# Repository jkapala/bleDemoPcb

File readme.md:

# Overview

This project started with the goal of building a circuit around the STM32 architecture and incorporate various features to evaluate them, which are called out in the Specifications document. A major goal of the project was also to document the project here, making sure to share my progress and use version control. Namely, I wanted to build a board to utilize BLE/WiFi directly, using a PIFA PCB or ceramic chip antenna, instead of using a Wireless module PCB as I have done in the past. As that is the primary goal of the project, other features were secondary but I was able to incorporate a lot of the initial specifications I made and even add some that could lend themselves to a compelling demo of the board. Unfortunately, the STM line of chips does not support WiFi so it was decided that it should be exluded from the project and BLE will be the primary wireless protocol used.

The firmware can be located at this repository: https://github.com/jkapala/bleDemoFirmware

**System Diagram**

## 4/7/2025 Update

The Design Output document is done! I have now edited it and reviewed it so that it is now a complete draft that matches the layout and schematic. The schematic has also been reviewed and edited to fix little things and improve readibility. As well, a few changes were made to the schematic and layout. Namely, a header to access the USB VBUS rail after the current sense resitor has been added, a ground pin has been added to the analog input channel header, and the ESD diodes for the SD card were swapped for ones with lower breakdown/clamping voltage.

At this stage, I consider all the design files to be in good standing and in agreement with each other. The next step will be to generate a BOM and scrutinize the pinouts of the selected components to the schematics/layout files.

In summary, I believe this commit is a complete draft of both the schematic, layout, and design output.

**Top View**

**Bottom View**

**Layer View**

## 3/31/2025 Update

Layout of the PCB is finished! I do not expect to change very much now regarding the circuit design or changing the board in any major way. DRC check has run and there are no major issues remaining. Any additional changes should be mainly cosmetic in the PCB and organizational in the schematic files. An additional final check that could necessitate a change is to use the STM32Cube IDE to verify that the pinout for the peripherals is correct, though it was used throughout for this already. The final footprint should focus most interaction to the top of the board. For ease of mounting the referenced LCD character display to the board, a female 2.54mm socket can be attached to the back of the board and the mounting holes in the corners should be aligned so that the screen can be mounted using standoffs/screws.

**Top View**

**Bottom View**

**Layer View**

The schematic should also specify all part numbers in order to generate a BOM in a future commit. Some passives and minor components remain unspecified because of their generic or non-critical parameters, e.g. specific 0603 LEDs.

The next step is to finalize the Hardware Design Output file by editing the current document to remove extra information, unused part numbers, check individual circuit blocks, part schematics, etc etc.

## 3/18/2025 Update

Layout is coming along and I am making my way to the STM32 and audio blocks. I decided to get with a ceramic chip antenna instead of the PCB antenna to increase chance of successful RF performance since I don't have RF tools right now. As such, I am using the spatial feedback of the mapped blocks to make final changes in the schematic. For example, I am most likely going to omit the onboard speaker because it really isn't necessary and I can get the version with the plug instead and use that. It looks like I will want to plan to mount the display on the bottomside of the board, otherwise I will cover any exposed pins. This requires moving the connector. Once I get that and the audio block sorted, the rest of the placement should be fairly straightforward.

## 3/7/2025 Update

Layout has started! Finally. I have made a big push to wrap up the schematic layout and do any corresponding research into the various things I wanted to study while building the board, such as RF theory, audio theory, best high-speed layout practices, EMI/EMC topics, etc etc.
The schematic is largely done and should only need adjustment to address bugs or layout improvements. The layout itself is roughly mapped out and currently is sketched to support mounting the chosen LCD screen directly on top of the board, but this require sizeable footprint so I might scrap that idea as I get more blocks placed. I am currently in the stage of doing the rough placing of components relative to the center component (e.g. the STM32, USB PD chip, DC-DC regulators, audio DAC + amp, etc etc). The USB PD block is done and now I am moving on to the DC-DC converters to route power to the downstream circuitry.

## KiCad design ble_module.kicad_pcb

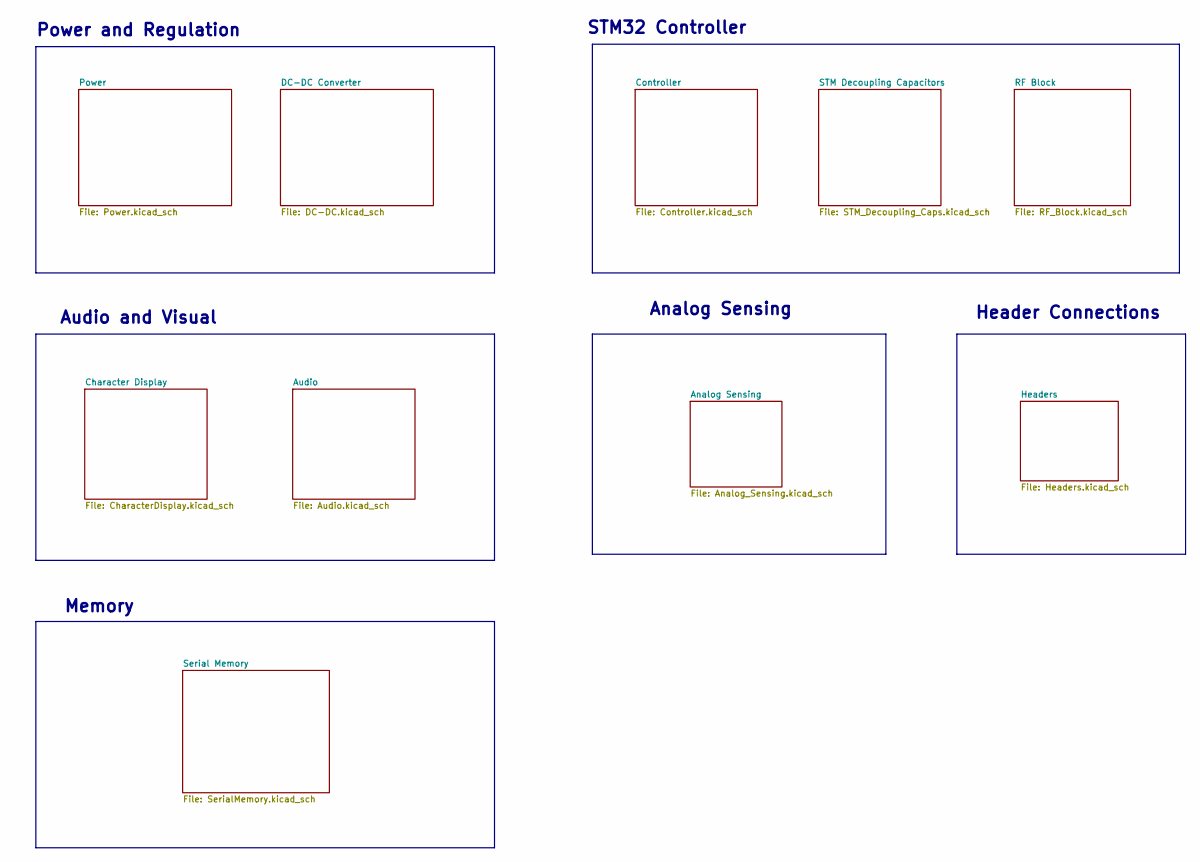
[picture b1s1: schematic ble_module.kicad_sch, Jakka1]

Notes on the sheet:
STM32 Controller
Header Connections
Memory
Power and Regulation
Analog Sensing
Audio and Visual

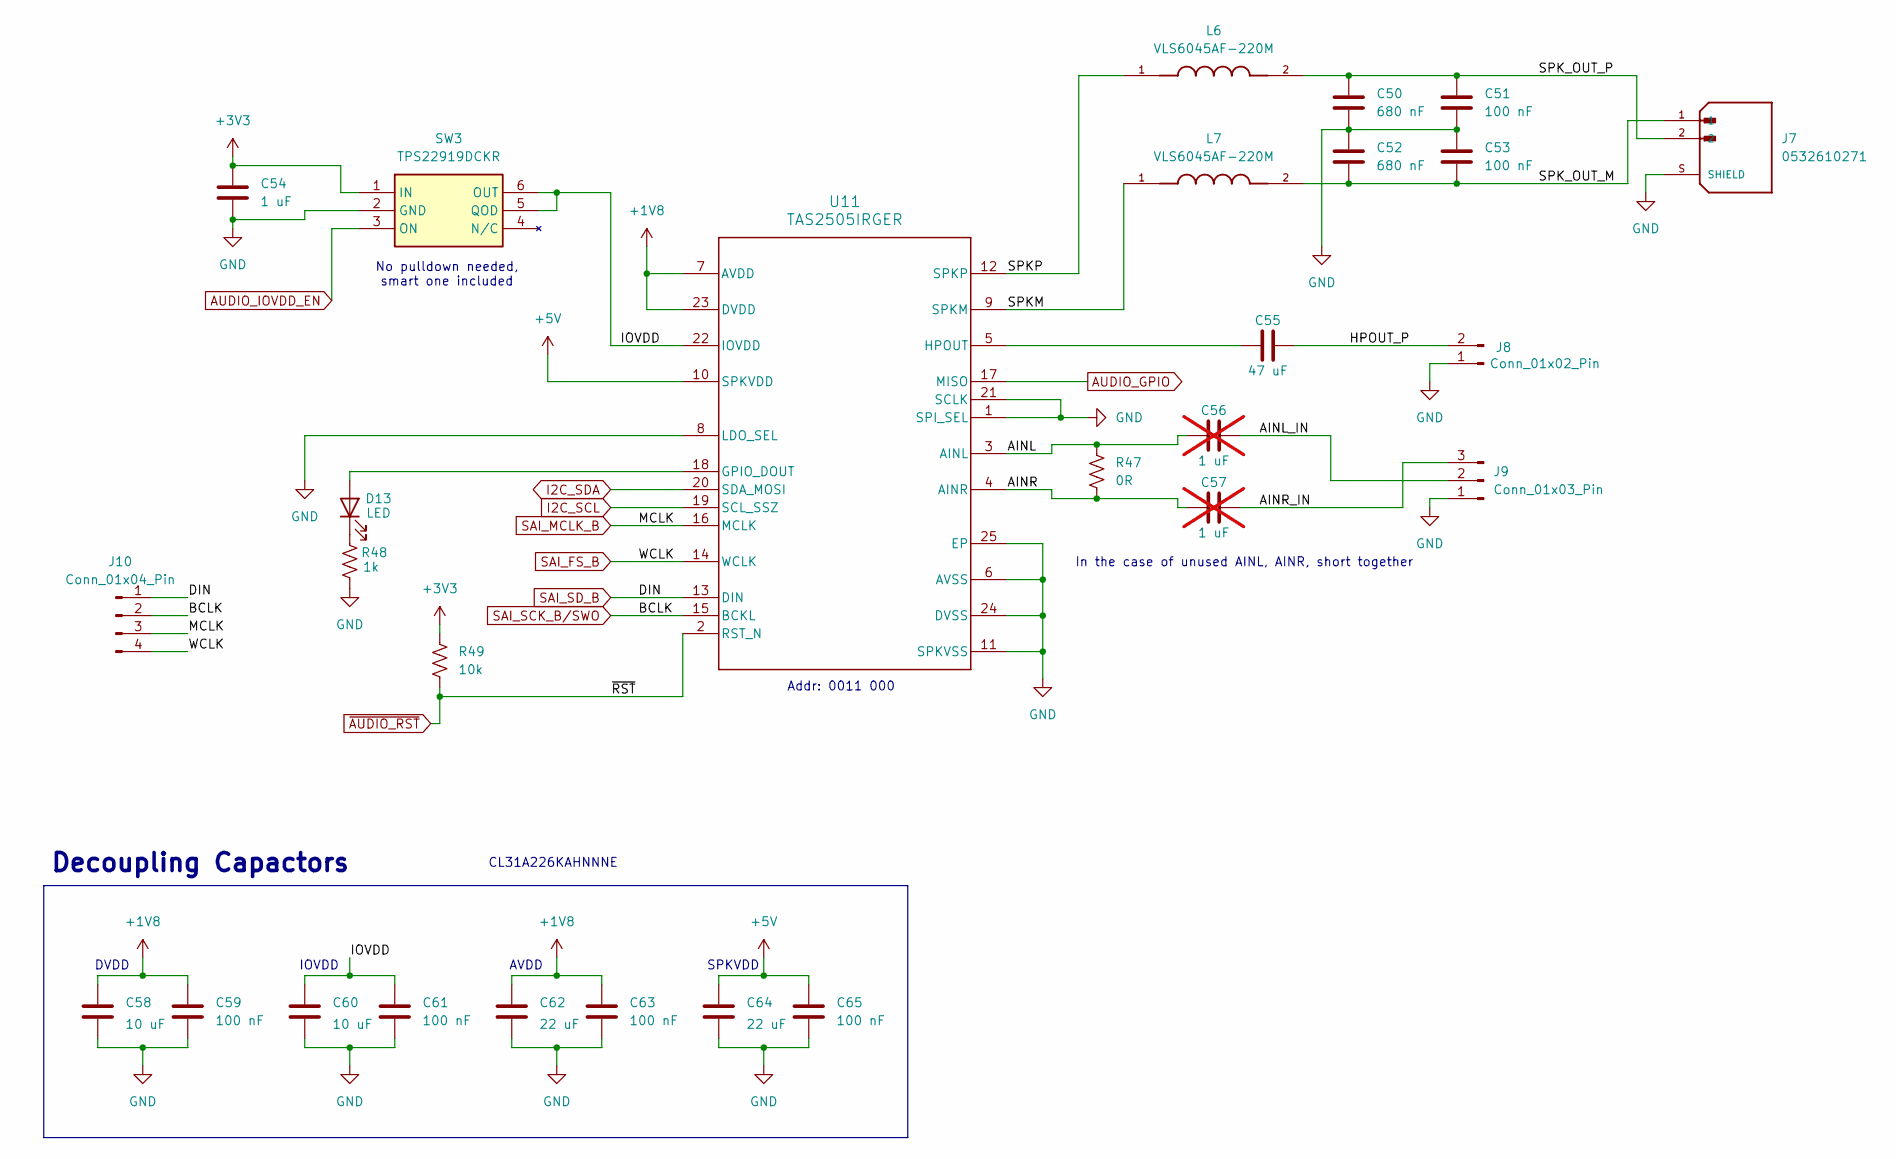
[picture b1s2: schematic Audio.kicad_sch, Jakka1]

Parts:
C50, C52: 680 nF; C_0603_1608Metric
C51, C53, C59, C61, C63, C65: 100 nF; C_0603_1608Metric
C54: 1 uF; C_0603_1608Metric
C55: 47 uF; C_1206_3216Metric
C56, C57: 1 uF; C_0603_1608Metric; not fitted
C58, C60: 10 uF; C_0805_2012Metric
C62, C64: 22 uF; C_1206_3216Metric
D13: LED; D_0603_1608Metric
J7: 0532610271; MOLEX_0532610271; PARTREV J
J8: Conn_01x02_Pin; PinHeader_1x02_P2.54mm_Vertical
J9: Conn_01x03_Pin; PinHeader_1x03_P2.54mm_Vertical
J10: Conn_01x04_Pin; PinHeader_1x04_P2.54mm_Vertical
L6, L7: VLS6045AF-220M; IND_VLS6045AF-220M; PARTREV N/A
R47: 0R; R_0603_1608Metric
R48: 1k; R_0603_1608Metric
R49: 10k; R_0603_1608Metric
SW3: TPS22919DCKR; SOT65P210X110-6N; Manufacturer_Part_Number TPS22919DCKR; Mouser Part Number 595-TPS22919DCKR
U11: TAS2505IRGER; TAS2505IR

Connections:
+1V8: C58.1, C59.1, C62.1, C63.1, U11.7 (AVDD), U11.23 (DVDD); also elsewhere on the board
+3V3: C54.1, R49.1, SW3.1 (IN); also elsewhere on the board
+5V: C64.1, C65.1, U11.10 (SPKVDD); also elsewhere on the board
/Audio/AINL: C56.1, R47.1, U11.3 (AINL)
/Audio/AINL_IN: C56.2, J9.2
/Audio/AINR: C57.1, R47.2, U11.4 (AINR)
/Audio/AINR_IN: C57.2, J9.3
/Audio/HPOUT_P: C55.2, J8.2
/Audio/IOVDD: C60.1, C61.1, SW3.5 (QOD), SW3.6 (OUT), U11.22 (IOVDD)
/Audio/SPKM: L7.1, U11.9 (SPKM)
/Audio/SPKP: L6.1, U11.12 (SPKP)
/Audio/SPK_OUT_M: C52.2, C53.2, J7.1, L7.2
/Audio/SPK_OUT_P: C50.1, C51.1, J7.2, L6.2
AUDIO_GPIO: U11.17 (MISO); also elsewhere on the board
AUDIO_IOVDD_EN: SW3.3 (ON); also elsewhere on the board
GND: C50.2, C51.2, C52.1, C53.1, C54.2, C58.2, C59.2, C60.2, C61.2, C62.2, C63.2, C64.2, C65.2, J7.S (SHIELD), J8.1, J9.1, R48.2, SW3.2 (GND), U11.1 (SPI_SEL), U11.6 (AVSS), U11.8 (LDO_SEL), U11.11 (SPKVSS), U11.21 (SCLK), U11.24 (DVSS), U11.25 (EP); also elsewhere on the board
I2C_SCL: U11.19 (SCL_SSZ); also elsewhere on the board
I2C_SDA: U11.20 (SDA_MOSI); also elsewhere on the board
unnamed: D13.2 (A), U11.18 (GPIO_DOUT)
unnamed: D13.1 (K), R48.1
unnamed: C55.1, U11.5 (HPOUT)
SAI_FS_B: J10.4, U11.14 (WCLK); also elsewhere on the board
SAI_MCLK_B: J10.3, U11.16 (MCLK); also elsewhere on the board
SAI_SCK_B/SWO: J10.2, U11.15 (BCKL); also elsewhere on the board
SAI_SD_B: J10.1, U11.13 (DIN); also elsewhere on the board
~AUDIO_RST: R49.2, U11.2 (RST_N); also elsewhere on the board

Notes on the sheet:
IOVDD
CL31A226KAHNNNE
In the case of unused AINL, AINR, short together
DVDD
Addr: 0011 000
SPKVDD
No pulldown needed, smart one included
Decoupling Capactors
AVDD

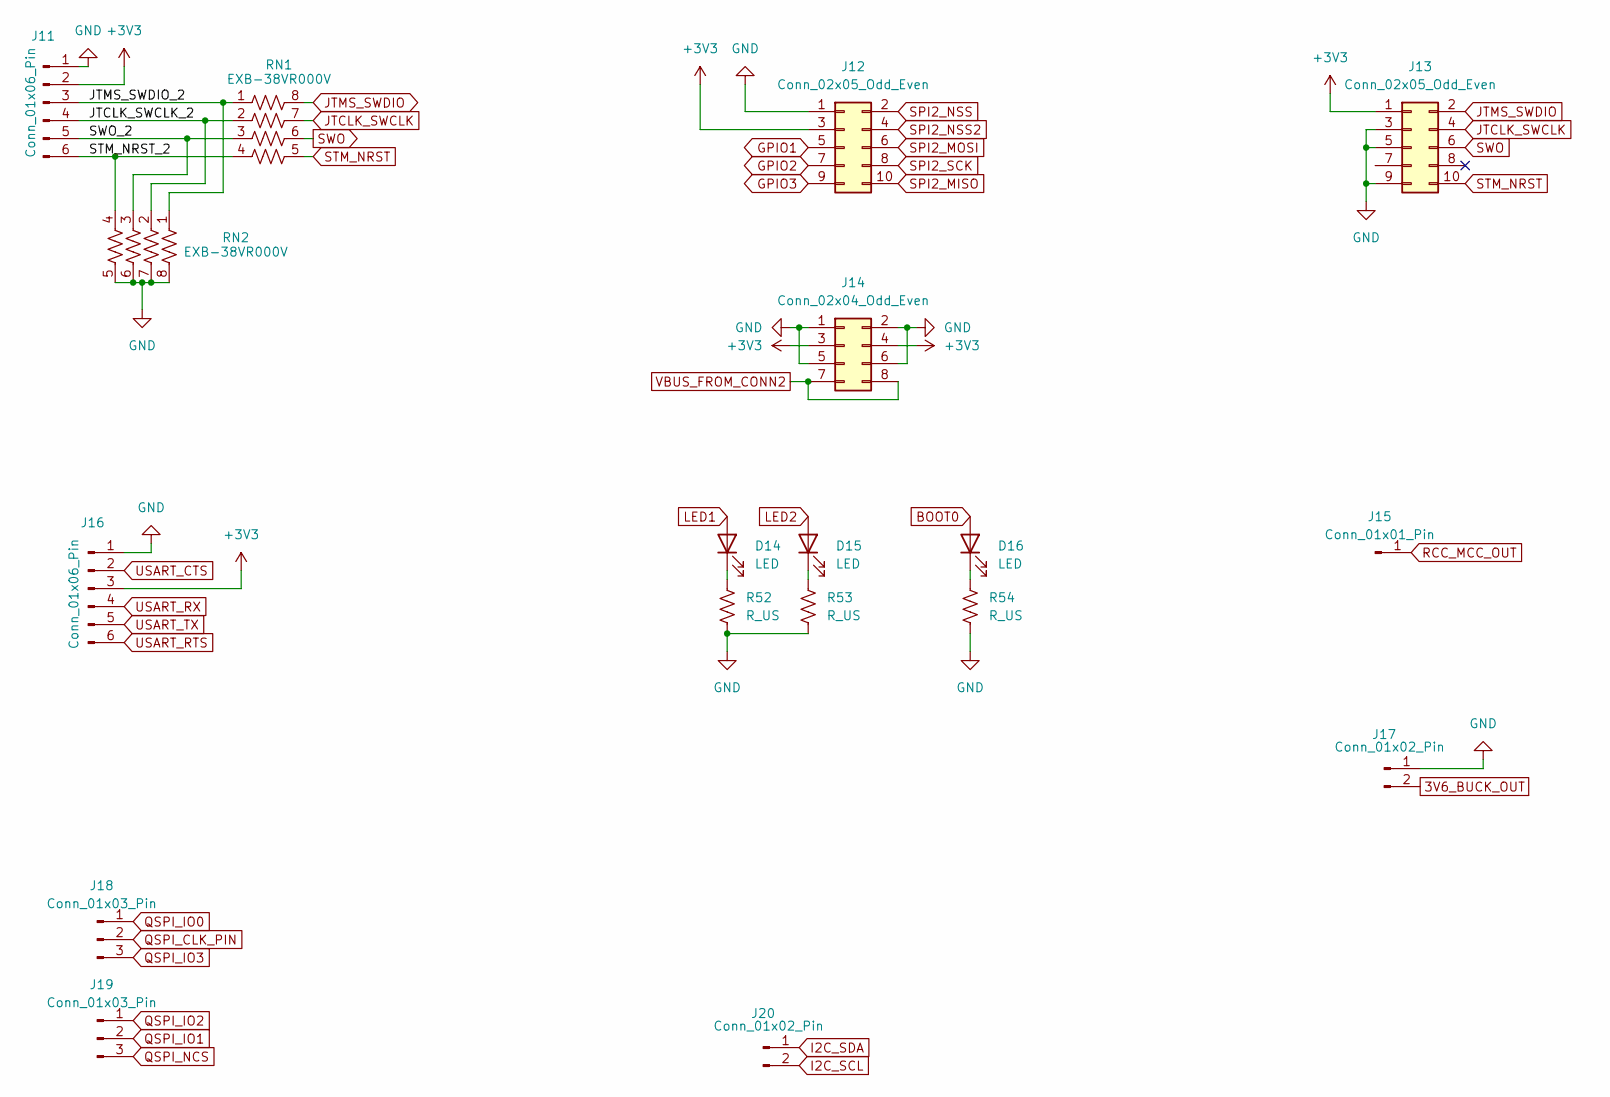
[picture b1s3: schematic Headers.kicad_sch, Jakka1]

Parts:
D14, D15, D16: LED; D_0603_1608Metric
J11, J16: Conn_01x06_Pin; PinHeader_1x06_P2.54mm_Vertical
J12: Conn_02x05_Odd_Even; PinHeader_2x05_P2.54mm_Vertical
J13: Conn_02x05_Odd_Even; PinHeader_2x05_P1.27mm_Vertical
J14: Conn_02x04_Odd_Even; PinHeader_2x04_P2.54mm_Vertical
J15: Conn_01x01_Pin; PinHeader_1x01_P2.54mm_Vertical
J17, J20: Conn_01x02_Pin; PinHeader_1x02_P2.54mm_Vertical
J18, J19: Conn_01x03_Pin; PinHeader_1x03_P2.54mm_Vertical
R52, R53, R54: R_US; R_0603_1608Metric
RN1, RN2: EXB-38VR000V; EXB38V472JV

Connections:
3V6_BUCK_OUT: J17.2; also elsewhere on the board
+3V3: J11.2, J12.3, J13.1, J14.3, J14.4, J16.3; also elsewhere on the board
/Headers/JTCLK_SWCLK_2: J11.4, RN1.2, RN2.2
/Headers/JTMS_SWDIO_2: J11.3, RN1.1, RN2.1
/Headers/STM_NRST_2: J11.6, RN1.4, RN2.4
/Headers/SWO_2: J11.5, RN1.3, RN2.3
BOOT0: D16.2 (A); also elsewhere on the board
GND: J11.1, J12.1, J13.3, J13.5, J13.9, J14.1, J14.2, J14.5, J14.6, J16.1, J17.1, R52.2, R53.2, R54.2, RN2.5, RN2.6, RN2.7, RN2.8; also elsewhere on the board
GPIO1: J12.5; also elsewhere on the board
GPIO2: J12.7; also elsewhere on the board
GPIO3: J12.9; also elsewhere on the board
I2C_SCL: J20.2; also elsewhere on the board
I2C_SDA: J20.1; also elsewhere on the board
JTCLK_SWCLK: J13.4, RN1.7; also elsewhere on the board
JTMS_SWDIO: J13.2, RN1.8; also elsewhere on the board
LED1: D14.2 (A); also elsewhere on the board
LED2: D15.2 (A); also elsewhere on the board
unnamed: D14.1 (K), R52.1
unnamed: D15.1 (K), R53.1
unnamed: D16.1 (K), R54.1
QSPI_CLK_PIN: J18.2; also elsewhere on the board
QSPI_IO0: J18.1; also elsewhere on the board
QSPI_IO1: J19.2; also elsewhere on the board
QSPI_IO2: J19.1; also elsewhere on the board
QSPI_IO3: J18.3; also elsewhere on the board
QSPI_NCS: J19.3; also elsewhere on the board
RCC_MCC_OUT: J15.1; also elsewhere on the board
SPI2_MISO: J12.10; also elsewhere on the board
SPI2_MOSI: J12.6; also elsewhere on the board
SPI2_NSS: J12.2; also elsewhere on the board
SPI2_NSS2: J12.4; also elsewhere on the board
SPI2_SCK: J12.8; also elsewhere on the board
STM_NRST: J13.10, RN1.5; also elsewhere on the board
SWO: J13.6, RN1.6; also elsewhere on the board
USART_CTS: J16.2
USART_RTS: J16.6
USART_RX: J16.4; also elsewhere on the board
USART_TX: J16.5; also elsewhere on the board
VBUS_FROM_CONN2: J14.7, J14.8; also elsewhere on the board

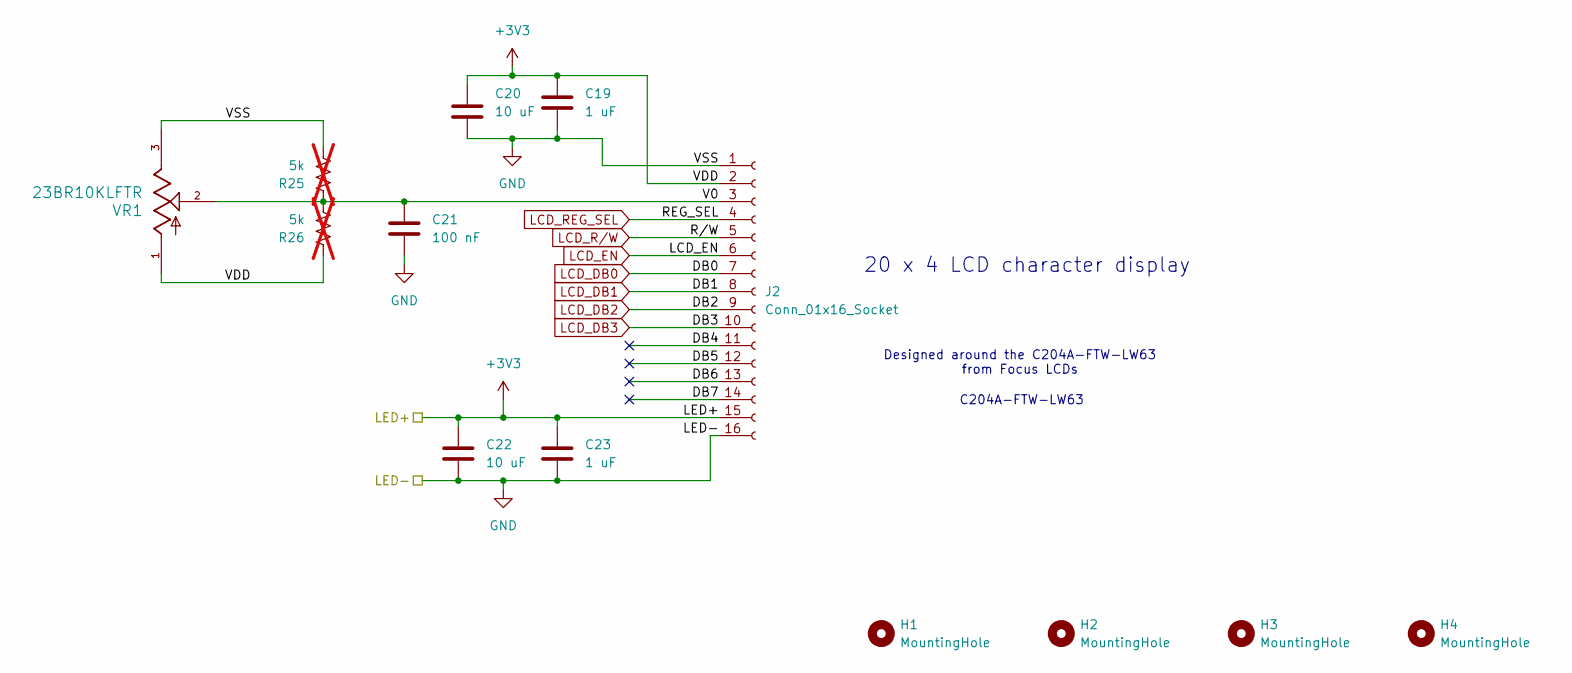
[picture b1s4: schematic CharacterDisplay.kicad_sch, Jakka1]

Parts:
C19, C23: 1 uF; C_0805_2012Metric
C20, C22: 10 uF; C_0805_2012Metric
C21: 100 nF; C_0603_1608Metric
H1, H2, H3, H4: MountingHole; MountingHole_3.2mm_M3
J2: Conn_01x16_Socket; PinSocket_1x16_P2.54mm_Vertical
R25, R26: 5k; R_0603_1608Metric; not fitted
VR1: 23BR10KLFTR; SOT_10KLFTR_BIT

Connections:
+3V3: C19.2, C20.2, C22.2, C23.2, J2.2, J2.15, R26.1, VR1.1; also elsewhere on the board
/Character Display/DB4: J2.11
/Character Display/DB5: J2.12
/Character Display/DB6: J2.13
/Character Display/DB7: J2.14
/Character Display/V0: C21.2, J2.3, R25.1, R26.2, VR1.2
GND: C19.1, C20.1, C21.1, C22.1, C23.1, J2.1, J2.16, R25.2, VR1.3; also elsewhere on the board
LCD_DB0: J2.7; also elsewhere on the board
LCD_DB1: J2.8; also elsewhere on the board
LCD_DB2: J2.9; also elsewhere on the board
LCD_DB3: J2.10; also elsewhere on the board
LCD_EN: J2.6; also elsewhere on the board
LCD_REG_SEL: J2.4; also elsewhere on the board
LCD_R/W: J2.5; also elsewhere on the board

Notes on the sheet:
C204A-FTW-LW63
20 x 4 LCD character display
Designed around the C204A-FTW-LW63 from Focus LCDs

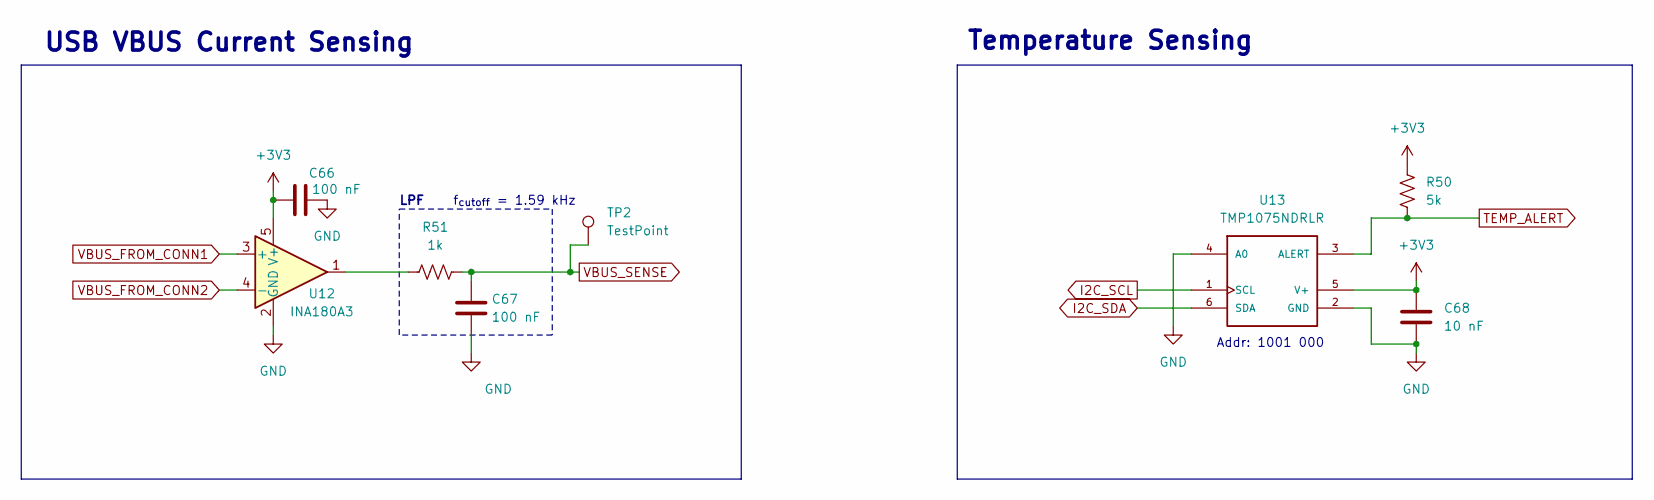
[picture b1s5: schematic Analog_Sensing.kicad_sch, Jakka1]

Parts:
C66, C67: 100 nF; C_0603_1608Metric
C68: 10 nF; C_0603_1608Metric
R50: 5k; R_0603_1608Metric
R51: 1k; R_0603_1608Metric
TP2: TestPoint; TestPoint_Pad_D1.0mm
U12: INA180A3; SOT-23-5
U13: TMP1075NDRLR; SOT50P160X60-6N; PARTREV E

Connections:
+3V3: C66.1, C68.1, R50.2, U12.5 (V+), U13.5 (V+); also elsewhere on the board
GND: C66.2, C67.1, C68.2, U12.2 (GND), U13.2 (GND), U13.4 (A0); also elsewhere on the board
I2C_SCL: U13.1 (SCL); also elsewhere on the board
I2C_SDA: U13.6 (SDA); also elsewhere on the board
unnamed: R51.1, U12.1
TEMP_ALERT: R50.1, U13.3 (ALERT); also elsewhere on the board
VBUS_FROM_CONN1: U12.3 (+); also elsewhere on the board
VBUS_FROM_CONN2: U12.4 (-); also elsewhere on the board
VBUS_SENSE: C67.2, R51.2, TP2.1; also elsewhere on the board

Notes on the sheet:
LPF
Addr: 1001 000
Temperature Sensing
f_{cutoff} = 1.59 kHz
USB VBUS Current Sensing

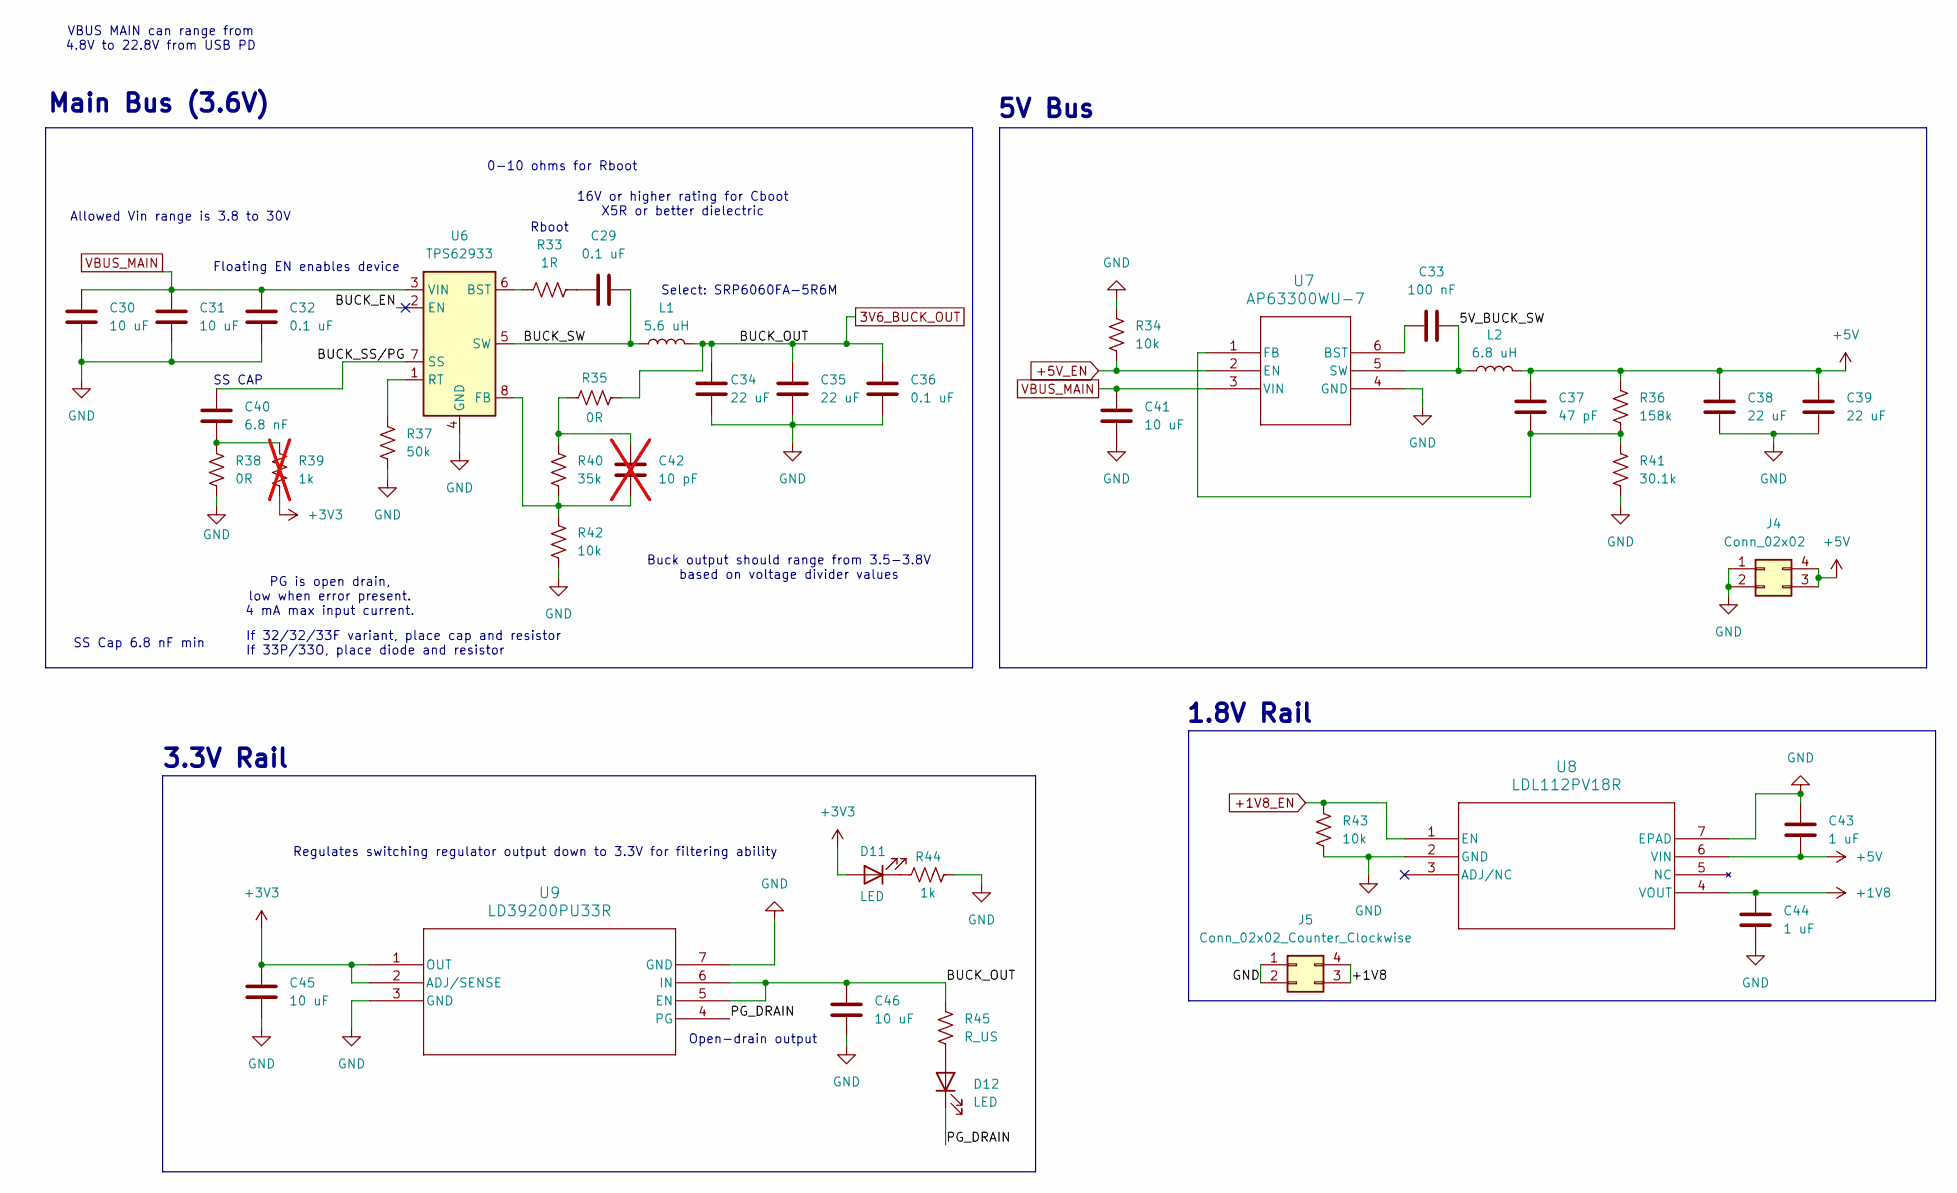
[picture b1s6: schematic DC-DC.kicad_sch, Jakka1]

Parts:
C29, C32, C36: 0.1 uF; C_0603_1608Metric
C30, C31, C41: 10 uF; C_1210_3225Metric
C33: 100 nF; C_0603_1608Metric
C34, C35: 22 uF; C_1210_3225Metric
C37: 47 pF; C_0603_1608Metric
C38, C39: 22 uF; C_1206_3216Metric
C40: 6.8 nF; C_0603_1608Metric
C42: 10 pF; C_0603_1608Metric; not fitted
C43, C44: 1 uF; C_0603_1608Metric
C45, C46: 10 uF; C_0805_2012Metric
D11, D12: LED; D_0603_1608Metric
J4: Conn_02x02; PinHeader_2x02_P2.54mm_Vertical
J5: Conn_02x02_Counter_Clockwise; PinHeader_2x02_P2.54mm_Vertical
L1: 5.6 uH; SRP6060FA5R6M
L2: 6.8 uH; SRP6060FA5R6M
R33: 1R; R_0603_1608Metric
R34, R42, R43: 10k; R_0603_1608Metric
R35, R38: 0R; R_0603_1608Metric
R36: 158k; R_0603_1608Metric
R37: 50k; R_0603_1608Metric
R39: 1k; R_0603_1608Metric; not fitted
R40: 35k; R_0603_1608Metric
R41: 30.1k; R_0603_1608Metric
R44: 1k; R_0603_1608Metric
R45: R_US; R_0603_1608Metric
U6: TPS62933; SOT-583-8
U7: AP63300WU-7; TSOT6_AP63300WU-7_DIO
U8: LDL112PV18R; DFN6_3P1X3P1X0P95_STM
U9: LD39200PU33R; SON_DFN6_3X3_STM-L

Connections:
3V6_BUCK_OUT: C34.1, C35.1, C36.1, C46.1, L1.2, R35.2, R45.1, U9.5 (EN), U9.6 (IN); also elsewhere on the board
+1V8: C44.1, J5.3, J5.4, U8.4 (VOUT); also elsewhere on the board
+1V8_EN: R43.2, U8.1 (EN); also elsewhere on the board
+3V3: C45.1, D11.2 (A), R39.1, U9.1 (OUT), U9.2 (ADJ/SENSE); also elsewhere on the board
+5V: C37.1, C38.1, C39.1, C43.2, J4.3, J4.4, L2.2, R36.2, U8.6 (VIN); also elsewhere on the board
+5V_EN: R34.2, U7.2 (EN); also elsewhere on the board
/DC-DC Converter/5V_BUCK_SW: C33.2, L2.1, U7.5 (SW)
/DC-DC Converter/BUCK_EN: U6.2 (EN)
/DC-DC Converter/BUCK_SS/PG: C40.1, U6.7 (SS)
/DC-DC Converter/BUCK_SW: C29.2, L1.1, U6.5 (SW)
/DC-DC Converter/PG_DRAIN: D12.1 (K), U9.4 (PG)
GND: C30.2, C31.2, C32.2, C34.2, C35.2, C36.2, C38.2, C39.2, C41.2, C43.1, C44.2, C45.2, C46.2, J4.1, J4.2, J5.1, J5.2, R34.1, R37.1, R38.1, R41.1, R42.1, R43.1, R44.2, U6.4 (GND), U7.4 (GND), U8.2 (GND), U8.7 (EPAD), U9.3 (GND), U9.7 (GND); also elsewhere on the board
unnamed: C29.1, R33.2
unnamed: C40.2, R38.2, R39.2
unnamed: C42.1, R35.1, R40.2
unnamed: D11.1 (K), R44.1
unnamed: D12.2 (A), R45.2
unnamed: R33.1, U6.6 (BST)
unnamed: C42.2, R40.1, R42.2, U6.8 (FB)
unnamed: R37.2, U6.1 (RT)
unnamed: C33.1, U7.6 (BST)
unnamed: C37.2, R36.1, R41.2, U7.1 (FB)
VBUS_MAIN: C30.1, C31.1, C32.1, C41.1, U6.3 (VIN), U7.3 (VIN); also elsewhere on the board

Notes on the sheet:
Buck output should range from 3.5-3.8V based on voltage divider values
SS Cap 6.8 nF min
Select: SRP6060FA-5R6M
Allowed Vin range is 3.8 to 30V
16V or higher rating for Cboot X5R or better dielectric
If 32/32/33F variant, place cap and resistor If 33P/33O, place diode and resistor
0-10 ohms for Rboot
5V Bus
PG is open drain, low when error present. 4 mA max input current.
Rboot
Floating EN enables device
Open-drain output
Regulates switching regulator output down to 3.3V for filtering ability
3.3V Rail
Main Bus (3.6V)
SS CAP
1.8V Rail
VBUS MAIN can range from 4.8V to 22.8V from USB PD

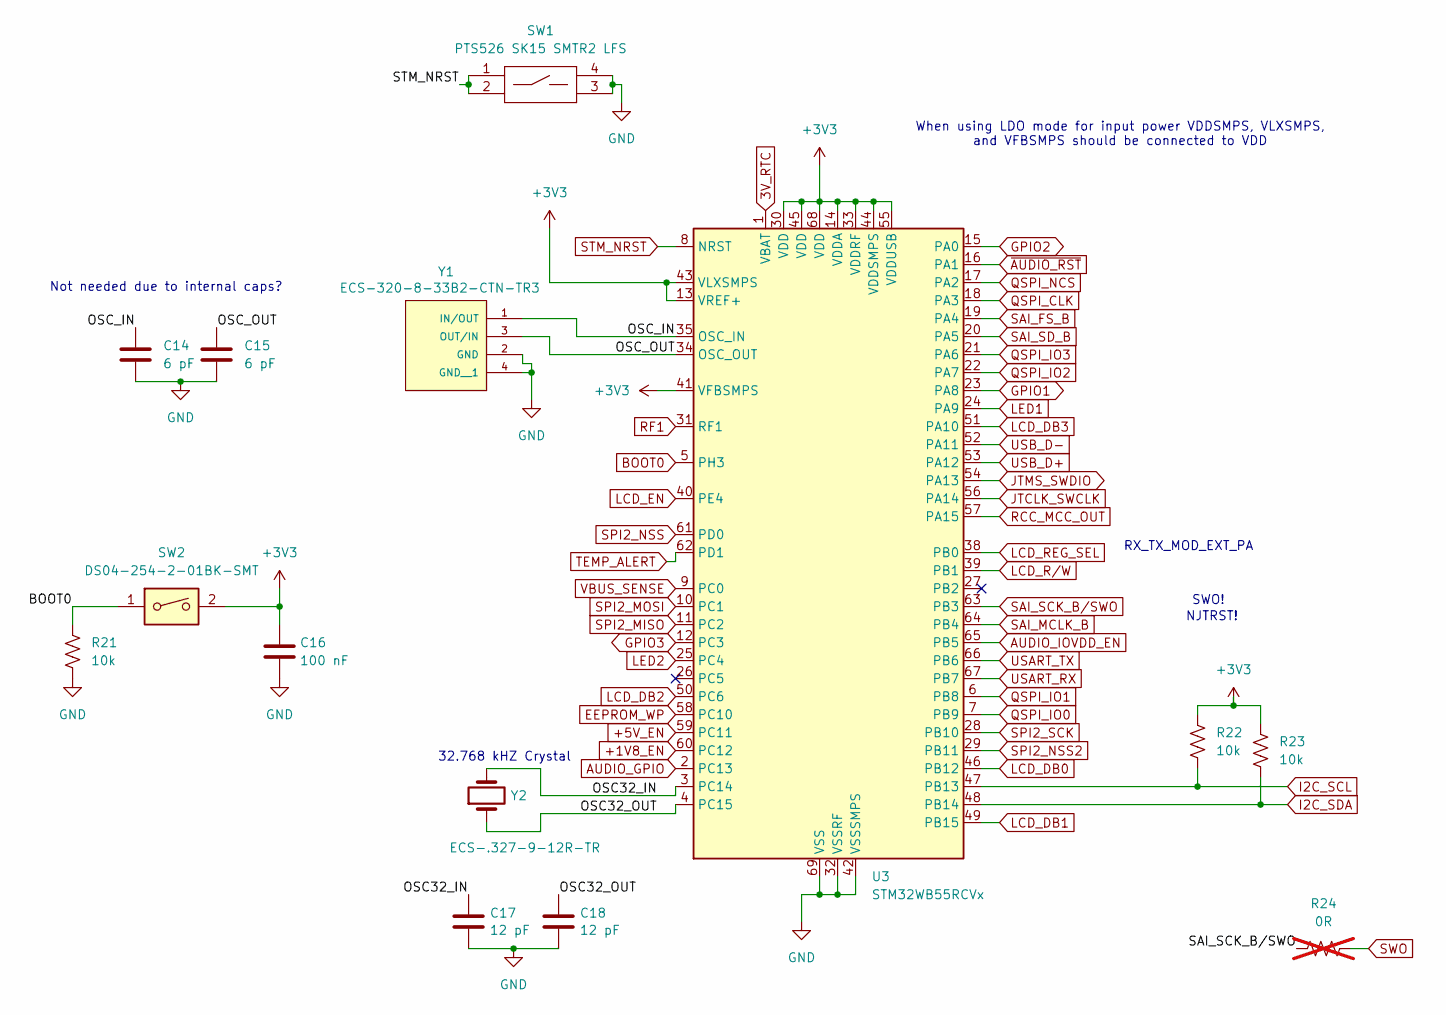
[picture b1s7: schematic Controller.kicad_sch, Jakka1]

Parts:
C14, C15: 6 pF; C_0603_1608Metric
C16: 100 nF; C_0603_1608Metric
C17, C18: 12 pF; C_0603_1608Metric
R21, R22, R23: 10k; R_0603_1608Metric
R24: 0R; R_0603_1608Metric; not fitted
SW1: PTS526 SK15 SMTR2 LFS; PTS526SK15SMTR2 LFS
SW2: DS04-254-2-01BK-SMT; DS04254201BKSMT; Manufacturer_Part_Number DS04-254-2-01BK-SMT; Mouser Part Number 490-DS04254201BK-SMT
U3: STM32WB55RCVx; QFN-68-1EP_8x8mm_P0.4mm_EP6.4x6.4mm
Y1: ECS-320-8-33B2-CTN-TR3; XTAL_ECS-320-8-33-RWY-TR
Y2: ECS-.327-9-12R-TR; Crystal_SMD_2012-2Pin_2.0x1.2mm_HandSoldering

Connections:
3V_RTC: U3.1 (VBAT); also elsewhere on the board
+1V8_EN: U3.60 (PC12); also elsewhere on the board
+3V3: C16.1, R22.1, R23.1, SW2.2, U3.13 (VREF+), U3.14 (VDDA), U3.30 (VDD), U3.33 (VDDRF), U3.41 (VFBSMPS), U3.43 (VLXSMPS), U3.44 (VDDSMPS), U3.45 (VDD), U3.55 (VDDUSB), U3.68 (VDD); also elsewhere on the board
+5V_EN: U3.59 (PC11); also elsewhere on the board
/Controller/OSC32_IN: C17.1, U3.3 (PC14), Y2.2
/Controller/OSC32_OUT: C18.1, U3.4 (PC15), Y2.1
/Controller/OSC_IN: C14.1, U3.35 (OSC_IN), Y1.1 (IN/OUT)
/Controller/OSC_OUT: C15.1, U3.34 (OSC_OUT), Y1.3 (OUT/IN)
AUDIO_GPIO: U3.2 (PC13); also elsewhere on the board
AUDIO_IOVDD_EN: U3.65 (PB5); also elsewhere on the board
BOOT0: R21.1, SW2.1, U3.5 (PH3); also elsewhere on the board
EEPROM_WP: U3.58 (PC10); also elsewhere on the board
GND: C14.2, C15.2, C16.2, C17.2, C18.2, R21.2, SW1.3, SW1.4, U3.32 (VSSRF), U3.42 (VSSSMPS), U3.69 (VSS), Y1.2 (GND), Y1.4 (GND__1); also elsewhere on the board
GPIO1: U3.23 (PA8); also elsewhere on the board
GPIO2: U3.15 (PA0); also elsewhere on the board
GPIO3: U3.12 (PC3); also elsewhere on the board
I2C_SCL: R22.2, U3.47 (PB13); also elsewhere on the board
I2C_SDA: R23.2, U3.48 (PB14); also elsewhere on the board
JTCLK_SWCLK: U3.56 (PA14); also elsewhere on the board
JTMS_SWDIO: U3.54 (PA13); also elsewhere on the board
LCD_DB0: U3.46 (PB12); also elsewhere on the board
LCD_DB1: U3.49 (PB15); also elsewhere on the board
LCD_DB2: U3.50 (PC6); also elsewhere on the board
LCD_DB3: U3.51 (PA10); also elsewhere on the board
LCD_EN: U3.40 (PE4); also elsewhere on the board
LCD_REG_SEL: U3.38 (PB0); also elsewhere on the board
LCD_R/W: U3.39 (PB1); also elsewhere on the board
LED1: U3.24 (PA9); also elsewhere on the board
LED2: U3.25 (PC4); also elsewhere on the board
QSPI_CLK: U3.18 (PA3); also elsewhere on the board
QSPI_IO0: U3.7 (PB9); also elsewhere on the board
QSPI_IO1: U3.6 (PB8); also elsewhere on the board
QSPI_IO2: U3.22 (PA7); also elsewhere on the board
QSPI_IO3: U3.21 (PA6); also elsewhere on the board
QSPI_NCS: U3.17 (PA2); also elsewhere on the board
RCC_MCC_OUT: U3.57 (PA15); also elsewhere on the board
RF1: U3.31 (RF1); also elsewhere on the board
SAI_FS_B: U3.19 (PA4); also elsewhere on the board
SAI_MCLK_B: U3.64 (PB4); also elsewhere on the board
SAI_SCK_B/SWO: R24.1, U3.63 (PB3); also elsewhere on the board
SAI_SD_B: U3.20 (PA5); also elsewhere on the board
SPI2_MISO: U3.11 (PC2); also elsewhere on the board
SPI2_MOSI: U3.10 (PC1); also elsewhere on the board
SPI2_NSS: U3.61 (PD0); also elsewhere on the board
SPI2_NSS2: U3.29 (PB11); also elsewhere on the board
SPI2_SCK: U3.28 (PB10); also elsewhere on the board
STM_NRST: SW1.1, SW1.2, U3.8 (NRST); also elsewhere on the board
SWO: R24.2; also elsewhere on the board
TEMP_ALERT: U3.62 (PD1); also elsewhere on the board
USART_RX: U3.67 (PB7); also elsewhere on the board
USART_TX: U3.66 (PB6); also elsewhere on the board
USB_D+: U3.53 (PA12); also elsewhere on the board
USB_D-: U3.52 (PA11); also elsewhere on the board
VBUS_SENSE: U3.9 (PC0); also elsewhere on the board
~AUDIO_RST: U3.16 (PA1); also elsewhere on the board

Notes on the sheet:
Not needed due to internal caps?
RX_TX_MOD_EXT_PA
NJTRST!
32.768 kHZ Crystal
SWO!
When using LDO mode for input power VDDSMPS, VLXSMPS, and VFBSMPS should be connected to VDD

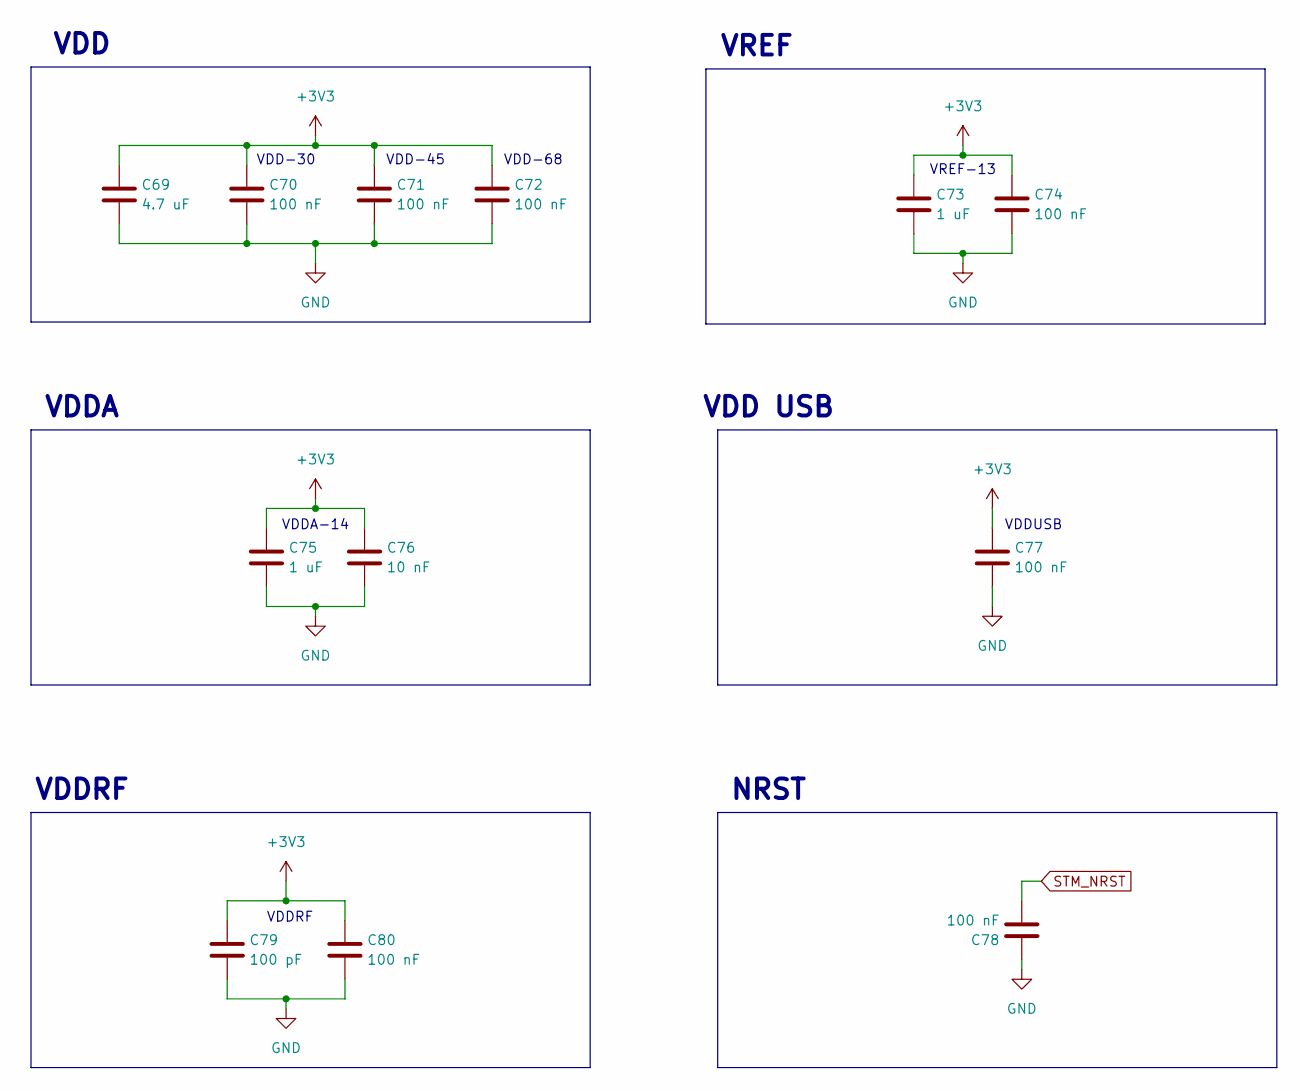
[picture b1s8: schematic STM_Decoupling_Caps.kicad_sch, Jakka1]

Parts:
C69: 4.7 uF; C_0805_2012Metric
C70, C71, C72, C74, C77, C78, C80: 100 nF; C_0603_1608Metric
C73, C75: 1 uF; C_0603_1608Metric
C76: 10 nF; C_0603_1608Metric
C79: 100 pF; C_0603_1608Metric

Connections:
+3V3: C69.1, C70.1, C71.1, C72.1, C73.1, C74.1, C75.1, C76.1, C77.1, C79.1, C80.1; also elsewhere on the board
GND: C69.2, C70.2, C71.2, C72.2, C73.2, C74.2, C75.2, C76.2, C77.2, C78.1, C79.2, C80.2; also elsewhere on the board
STM_NRST: C78.2; also elsewhere on the board

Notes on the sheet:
VREF
VDD USB
VDD-68
VDD-30
VDD-45
VDDRF
VDDRF
VDD
VDDA-14
VDDA
VDDUSB
NRST
VREF-13
